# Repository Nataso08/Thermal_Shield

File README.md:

# 💻 Thermal_Shield 🌡️

Un progetto Arduino per il controllo della temperatura tramite una scheda termica e una ventola. 
<br>

## 🧾 Materiali necessari:
- Arduino UNO
- Scheda termica
- Ventola 12 V
- Ponte H

## 🌡️ Scheda termica:
La scheda termica utilizzata nel nostro sistema è stata realizzata dalla nostra scuola, [Istituto Max Planck (Villorba, TV)](https://maxplanck.edu.it).

### 📐 Struttura:
La scheda termica è strutturata su un PCB e si presenta come riportato nelle seguenti immagini.
<br>

<div style="display:flex; gap:10px;">

</div>

### 🖇️ Schema
Di seguito è riportato lo schema elettrico della scheda. <br>

[Progetto Kicad](./Thermal_Shield/Thermal_Shield.kicad_pro)

### 🔌 Collegamenti:

- Alimentare la scheda (jack DC) ad una tensione di 12 V
- Collegare Arduino UNO tramite la morsettiera:
    - GND → GND
    - $V_T$ → Ingresso Analogico di Arduino (A0 - A5)
    - PWM → Uscita PWM di Arduino (pin 3, 5, 6, 9, 10 o 11)

## 💨 Ventola:
Generica ventola 12 V (es. ventola da PC).<br><br>

### 🔌 Collegamenti:
- Power → alimentazione 12 V (tramite [ponte H](#ponte-h))
- GND → GND (comune tra Arduino e alimentazione 12 V)
- RPM → Pin interrupt di Arudino (2, 3)

⚠️ **Non collegare GND all'uscita del ponte H, altrimenti l'encoder non funziona correttamente**. <br>
❗ Nel codice allegato non è presente la misurazione della velocità (RPM) ma è facilmente integrabile.

❗ Collegare 5 V del ponte H a $V_{in}$ di Arduino se si vuole far funzionare il sistema indipendente dall'alimentazione USB. <br>
⚠️ In questo caso, **alimentare il ponte H prima di collegare Arduino con USB** per evitare problemi di alimentazione.
<br><br>

### 🔌 Ponte H:
È possibile usare un qualsiasi ponte H. <br>
Nel mio caso ho utilizzato un L298N, utilizzando esclusivamente il "ramo" B. <br><br>

Collegare il pin IN3 (se si utilizza il "ramo" B) ad un'uscita PWM di Arduino (pin 3, 5, 6, 9, 10 o 11). <br>
⚠️ Si può verificare se il l'alimentazione ha polarizzazione corretta cortocircuitando il pin IN3 con i 5 V di Arduino: se la ventola inizia a girare il pin è corretto, altrimenti collegare il pin IN4 (o il complementare della coppia del "ramo" scelto).

#### ❗ Alternative:
Se non si dispone di un ponte H è possibile sostituirlo con un circuito a transistor con dovuto dimensionamento.
<br>

### ⚙️ Filtro segnale PWM:
Poiché il segnale PWM potrebbe non essere propriamente adatto alla tua ventola è consigliabile realizzare un filtro RC come quello di seguito riportato. <br>
...

## 🛠️ Setup:
1) Effettuare i collegamenti sopra descritti
2) Adattare i pin impostati nel [codice allegato](/Thermal_Shield.ino) sulla base delle proprie necessità
3) Impostare i propri valori di T_min e T_max
4) Se necessario, modificare il kp e q (nella funzione FTU) affinché la ventola riesca ad abbassare la temperatura fino a T_min
5) Caricare il [codice allegato](/Thermal_Shield.ino) e aggiornato (vedi punto 2) su Arduino tramite Arduino IDE

## 💻 Utilizzo:

### 🟢 Azionamento:
Si può azionare il sistema tramite:
1) Pressione del pulsante Start
2) Scrittura '1' su Seriale

A seguito di una delle 2 azioni il sistema inizierà il suo ciclo di riscaldamento/raffreddamento.

### 🔴 Spegnimento:
Si può fermare il sistema tramite:
1) Pressione del pulsante Stop
2) Scrittura '0' su Seriale

A seguito di una delle 2 azioni il sistema si fermerà togliendo alimentazione a resistenza riscaldante e ventola (non svolge però la funzione di freno alla ventola, che continuerà a ruotare per inerzia).

### 📊 Misurazione / rappresentazione grafica:
È possibile osservare il variare della temperatura tramite la lettura della comunicazione seriale. In particolare:
- **Monitor Seriale**: Permette una facile lettura dei dati "grezzi" 📄
- **Plotter Seriale**: Permette una facile visualizzazione grafica del variare dei valori 📉

<br>

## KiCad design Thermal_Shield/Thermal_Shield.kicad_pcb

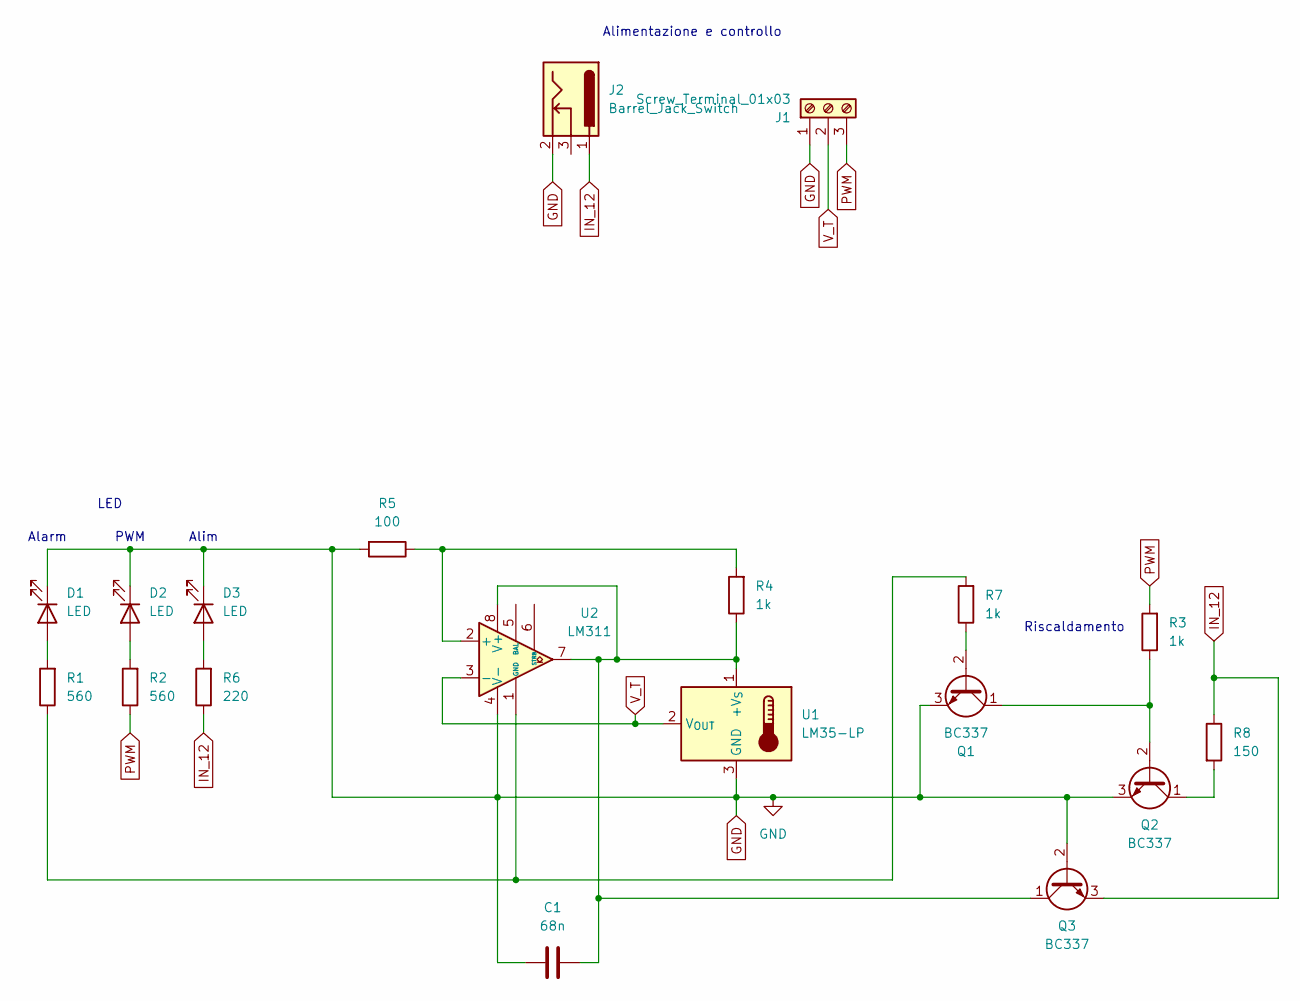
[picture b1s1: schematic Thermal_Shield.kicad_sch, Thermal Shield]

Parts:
C1: 68n; C_Rect_L7.2mm_W2.5mm_P5.00mm_FKS2_FKP2_MKS2_MKP2
D1, D2, D3: LED; LED_D4.0mm
J1: Screw_Terminal_01x03; TerminalBlock_MaiXu_MX126-5.0-03P_1x03_P5.00mm
J2: Barrel_Jack_Switch; BarrelJack_Horizontal
Q1, Q2, Q3: BC337; TO-92_Inline_Wide
R1, R2: 560; R_Axial_DIN0309_L9.0mm_D3.2mm_P12.70mm_Horizontal
R3, R4, R7: 1k; R_Axial_DIN0309_L9.0mm_D3.2mm_P12.70mm_Horizontal
R5: 100; R_Axial_DIN0309_L9.0mm_D3.2mm_P12.70mm_Horizontal
R6: 220; R_Axial_DIN0309_L9.0mm_D3.2mm_P12.70mm_Horizontal
R8: 150; R_Axial_DIN0309_L9.0mm_D3.2mm_P20.32mm_Horizontal
U1: LM35-LP; TO-92_Inline_Wide
U2: LM311; DIP-8_W7.62mm

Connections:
GND: C1.2, D1.1 (K), D2.1 (K), D3.1 (K), J1.1, J2.2, Q1.3 (E), Q2.3 (E), Q3.2 (B), R5.2, U1.3 (GND), U2.4 (V-)
IN_12: J2.1, Q3.3 (E), R6.1, R8.1
unnamed: D1.2 (A), R1.2
unnamed: D2.2 (A), R2.2
unnamed: D3.2 (A), R6.2
unnamed: Q1.2 (B), R7.1
unnamed: Q1.1 (C), Q2.2 (B), R3.1
unnamed: Q2.1 (C), R8.2
unnamed: C1.1, Q3.1 (C), R4.1, U1.1 (+V_{S}), U2.7, U2.8 (V+)
unnamed: R4.2, R5.1, U2.2 (+)
unnamed: R1.1, R7.2, U2.1 (GND)
PWM: J1.3, R2.1, R3.2
V_T: J1.2, U1.2 (V_{OUT}), U2.3 (-)

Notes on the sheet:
LED
Riscaldamento
PWM
Alim
Alarm
Alimentazione e controllo

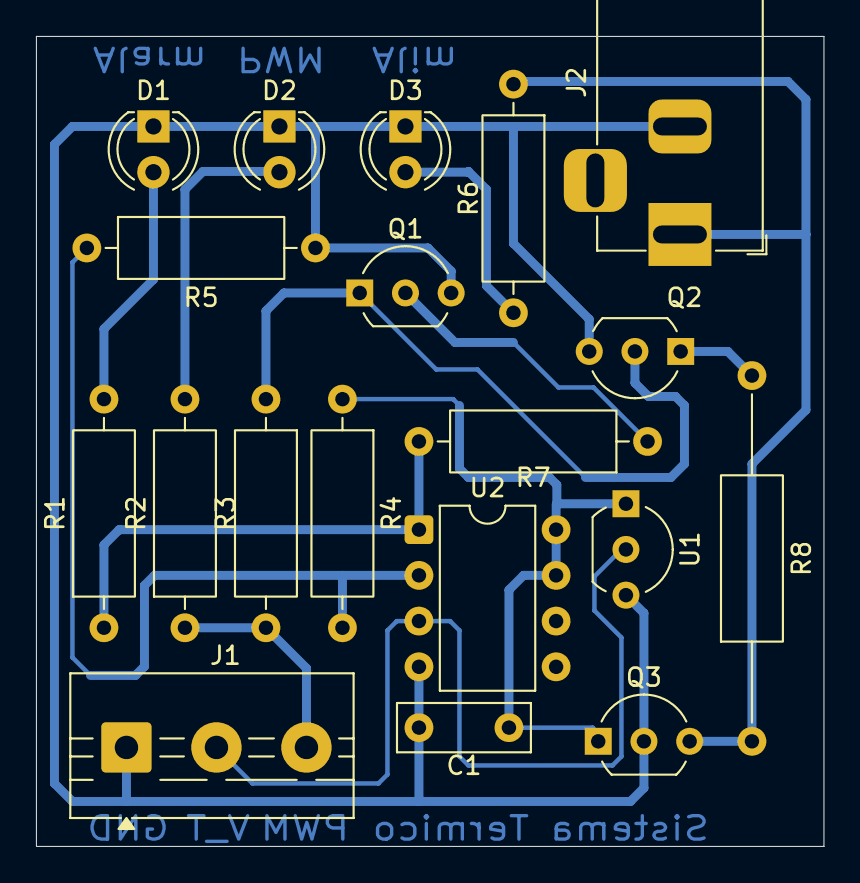
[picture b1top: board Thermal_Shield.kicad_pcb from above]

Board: 2 copper layers, 43.8 x 45.0 mm, 19 parts (0 on the bottom side), 13 nets.

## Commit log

2026-01-21 Codice Arduino della scheda termica (file .ino + libreria .h + datasheet LM35.pdf
2026-01-21 Update README.md & some code adds
2026-01-21 Better gif
2026-01-22 Refactor README formatting and remove line breaks
    Removed unnecessary line breaks and improved formatting in the README.
2026-02-07 School link in README.md
2026-02-07 Schematica
2026-02-08 PCB ready to connections
2026-02-09 Connections
